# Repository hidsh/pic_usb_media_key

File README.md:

# pic_usb_media_key

- IDE: MPLAB X v4.15
- compiler: C18 v3.46

## variant

### branch: hp_dso_pad

A quickfix for `RUN` and `STOP` buttons for DSOs [Agilent MSO8064A](https://www.keysight.com/en/pd-718231-pn-MSO8064A/infiniium-mixed-signal-oscilloscope-600-mhz-4-scope-and-16-digital-channels/).

## reference design

- [AE-PIC18F14K50](http://akizukidenshi.com/download/ds/akizuki/AE-PIC18F14K50.pdf)

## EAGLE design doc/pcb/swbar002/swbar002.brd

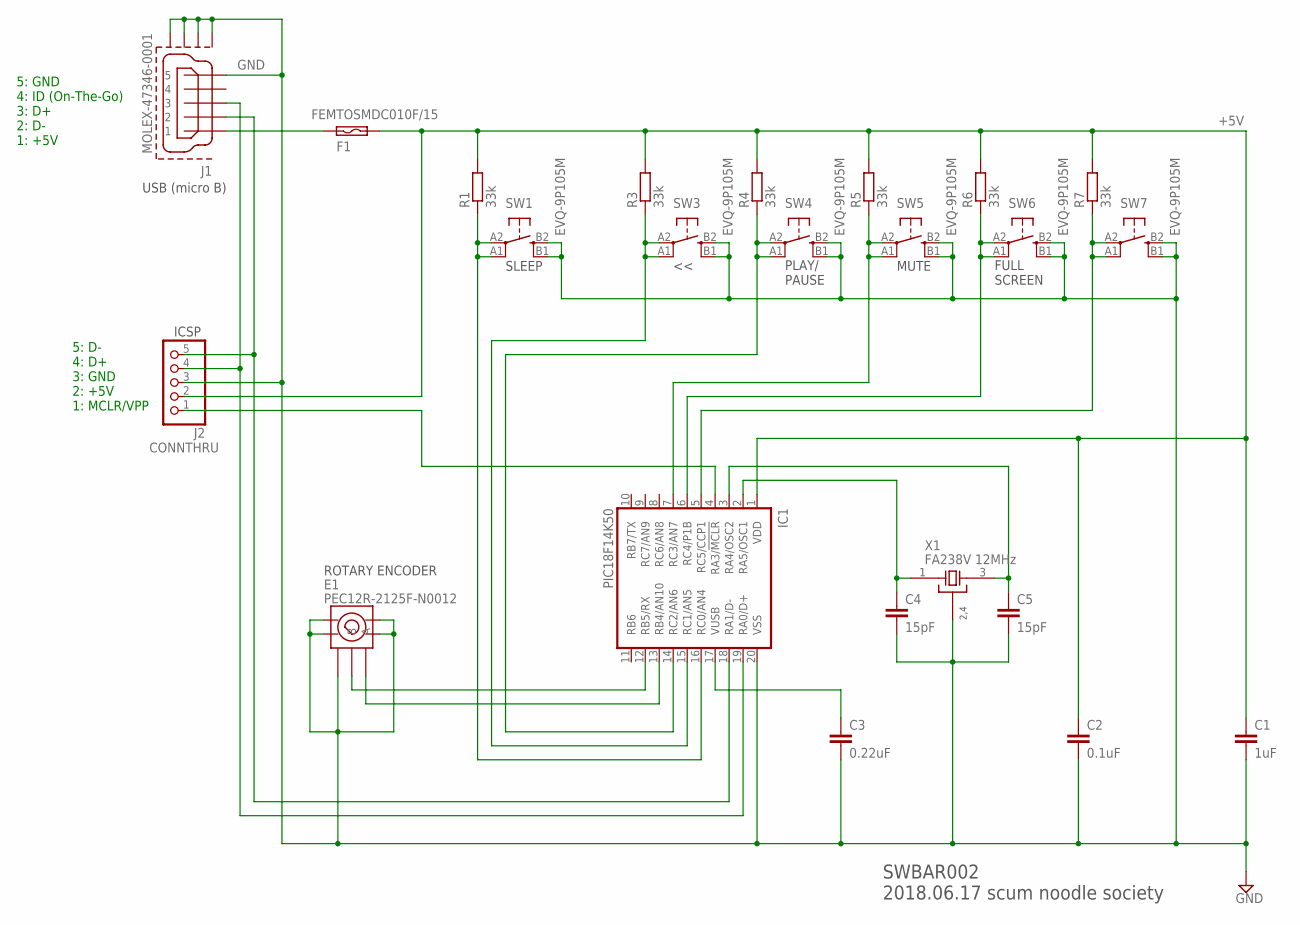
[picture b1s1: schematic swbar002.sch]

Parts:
C1: 1uF; C0603K
C2: 0.1uF; C0603K
C3: 0.22uF; C0603K
C4, C5: 15pF; C0603K
E1: PEC12R-2125F-N0012; PEC12R
F1: FEMTOSMDC010F/15; C0603K
IC1: PIC18F14K50; SSOP20
J1: MOLEX-47346-0001; MOLEX-47364-0001
J2: CONNTHRU; 1X05_CONNTHRU
R1, R3, R4, R5, R6, R7: 33k; R0603
SW1, SW3, SW4, SW5, SW6, SW7: EVQ-9P105M; EVQ9P
X1: FA238V 12MHz; XTAL_SMD_32X25

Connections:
+5V: C1.1, C2.1, F1.2, IC1.1 (VDD), J2.2, R1.2, R3.2, R4.2, R5.2, R6.2, R7.2
D+: IC1.19 (RA0/D+), J1.3, J2.4
D-: IC1.18 (RA1/D-), J1.2, J2.5
GND: C1.2, C2.2, C3.2, C4.2, C5.2, E1.GND@1 (GND), E1.GND@2 (GND), E1.GND@3 (GND), E1.GND@4 (GND), E1.GND@5 (GND), IC1.20 (VSS), J1.5, J1.GND1 (GND), J1.GND2 (GND), J1.GND3 (GND), J1.GND4 (GND), J2.3, SW1.B1 (G$S1), SW1.B2 (G$S2), SW3.B1 (G$S1), SW3.B2 (G$S2), SW4.B1 (G$S1), SW4.B2 (G$S2), SW5.B1 (G$S1), SW5.B2 (G$S2), SW6.B1 (G$S1), SW6.B2 (G$S2), SW7.B1 (G$S1), SW7.B2 (G$S2), X1.2 (GND), X1.4 (GND)
unnamed: IC1.16 (RC0/AN4), R1.1, SW1.A1 (G$P1), SW1.A2 (G$P2)
unnamed: E1.A, IC1.13 (RB4/AN10)
unnamed: IC1.5 (RC5/CCP1), R7.1, SW7.A1 (G$P1), SW7.A2 (G$P2)
unnamed: IC1.6 (RC4/P1B), R6.1, SW6.A1 (G$P1), SW6.A2 (G$P2)
unnamed: E1.B, IC1.12 (RB5/RX)
unnamed: IC1.7 (RC3/AN7), R5.1, SW5.A1 (G$P1), SW5.A2 (G$P2)
unnamed: IC1.14 (RC2/AN6), R4.1, SW4.A1 (G$P1), SW4.A2 (G$P2)
unnamed: IC1.4 (RA3/!MCLR!), J2.1
unnamed: IC1.15 (RC1/AN5), R3.1, SW3.A1 (G$P1), SW3.A2 (G$P2)
unnamed: C3.1, IC1.17 (VUSB)
unnamed: C5.1, IC1.3 (RA4/OSC2), X1.3 (X3)
unnamed: C4.1, IC1.2 (RA5/OSC1), X1.1 (X1)
VBUS: F1.1, J1.1

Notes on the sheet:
SLEEP
FULL SCREEN
MUTE
PLAY/ PAUSE
SWBAR002 2018.06.17 scum noodle society
5: GND 4: ID (On-The-Go) 3: D+ 2: D- 1: +5V
5: D- 4: D+ 3: GND 2: +5V 1: MCLR/VPP
USB (micro B)
ROTARY ENCODER
ICSP

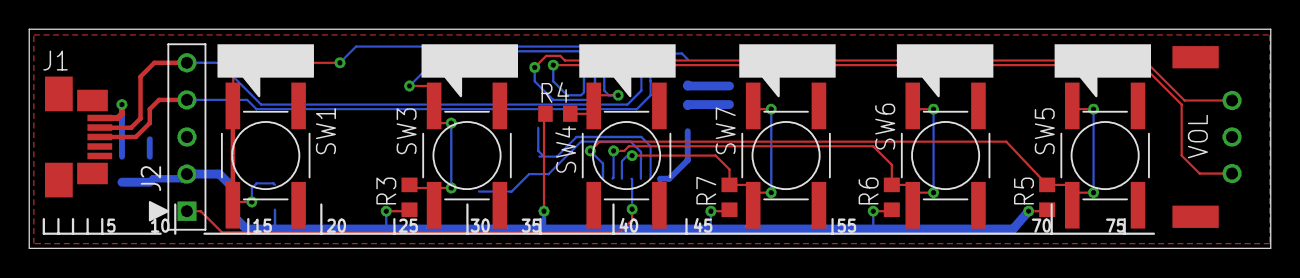
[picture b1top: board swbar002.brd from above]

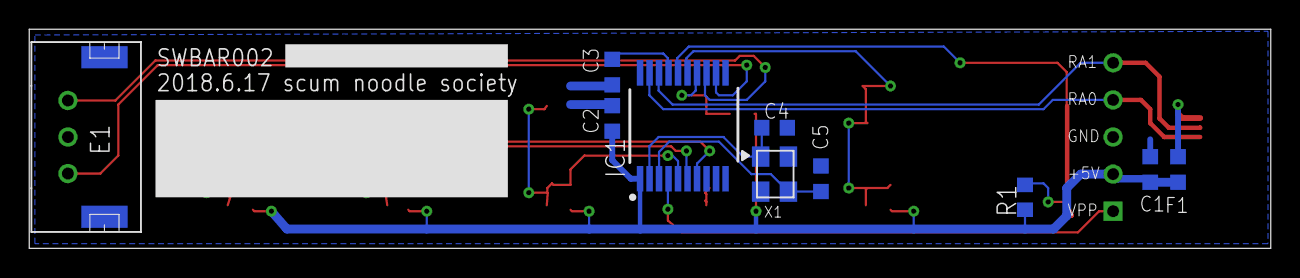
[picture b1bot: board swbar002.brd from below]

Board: 2 copper layers, 85.0 x 15.0 mm, 23 parts (10 on the bottom side), 17 nets.

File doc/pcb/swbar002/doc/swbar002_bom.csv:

"Part";"Value";"Device";"Package";"Description";"";
"C1";"1uF";"C-EUC0603K";"C0603K";"CAPACITOR, European symbol";"";
"C2";"0.1uF";"C-EUC0603K";"C0603K";"CAPACITOR, European symbol";"";
"C3";"0.22uF";"C-EUC0603K";"C0603K";"CAPACITOR, European symbol";"";
"C4";"15pF";"C-EUC0603K";"C0603K";"CAPACITOR, European symbol";"";
"C5";"15pF";"C-EUC0603K";"C0603K";"CAPACITOR, European symbol";"";
"E1";"PEC12R-2125F-N0012";"PEC12R-2125F-N0012";"PEC12R";"PEC12R-2125F-N0012,";"";
"F1";"FEMTOSMDC010F/15";"FEMTOSMDC010F/15";"C0603K";"Resettable Fuse";"";
"IC1";"PIC18F14K50";"PIC18F14K50";"SSOP20";"";"";
"J1";"MOLEX-47346-0001";"MOLEX-47346-0001";"MOLEX-47364-0001";"MICRO USB B, BOTTOM MOUNT";"";
"J2";"CONNTHRU";"PINHD-1X51X05_CONNTHRU";"1X05_CONNTHRU";"PIN HEADER";"";
"R1";"33k";"R-EU_R0603";"R0603";"RESISTOR, European symbol";"";
"R3";"33k";"R-EU_R0603";"R0603";"RESISTOR, European symbol";"";
"R4";"33k";"R-EU_R0603";"R0603";"RESISTOR, European symbol";"";
"R5";"33k";"R-EU_R0603";"R0603";"RESISTOR, European symbol";"";
"R6";"33k";"R-EU_R0603";"R0603";"RESISTOR, European symbol";"";
"R7";"33k";"R-EU_R0603";"R0603";"RESISTOR, European symbol";"";
"SW1";"EVQ-9P105M";"EVQ-9P105M";"EVQ9P";"Panasonic Tactile Switch";"";
"SW3";"EVQ-9P105M";"EVQ-9P105M";"EVQ9P";"Panasonic Tactile Switch";"";
"SW4";"EVQ-9P105M";"EVQ-9P105M";"EVQ9P";"Panasonic Tactile Switch";"";
"SW5";"EVQ-9P105M";"EVQ-9P105M";"EVQ9P";"Panasonic Tactile Switch";"";
"SW6";"EVQ-9P105M";"EVQ-9P105M";"EVQ9P";"Panasonic Tactile Switch";"";
"SW7";"EVQ-9P105M";"EVQ-9P105M";"EVQ9P";"Panasonic Tactile Switch";"";
"X1";"FA238V 12MHz";"FA-238V";"XTAL_SMD_32X25";"EPSON TOYOCOM FA238V, SMD, 4 PAD";"";

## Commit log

2015-11-21 import from "pic_usb_vol"
2015-11-22 sw --> input chararacter 'a'
2015-11-28 implemeted all functions
2015-11-29 released
2015-11-29 renamed images
2015-12-03 wakeup by any key
2015-12-03 add .gitattributes
2015-12-19 optimized jpg
2018-05-13 Add a Volume Controller and MUTE sw
2018-06-22 improve unbouncing to read encoder, behavior of sleep sw
2018-06-22 maintain
2018-07-15 correspond to new pcb(swbar002)
2018-07-21 add new pcb swbar002
